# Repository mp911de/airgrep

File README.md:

# airgrep

A portable ADS-B / FLARM receiver. Started as carrier board for a removable ESP32-S3 touch display and ADSBee 1090U receiver, with a soldered MAX-M10S GNSS receiver. It adds a single-cell Li-ion charger, a 5 V boost rail, a fuel gauge, a barometer and a buzzer.

## Current state

- Schematic (7 sheets) and board (105 x 95 mm, 4 layers, all SMD parts on top) are implemented. The active TI PCB and schematics define the hardware; `tools/check.sh` reports the ERC, DRC and parity state.
- Order status and open work are in [docs/open-issues.md](docs/open-issues.md).

## Where things are

| Path | Content |
|---|---|
| [docs/requirements.md](docs/requirements.md) | What the device must do. Read first. |
| [docs/checklist-draft.md](docs/checklist-draft.md) | Draft hardware review checks, investigation guidance and trial evaluation |
| [docs/specs.md](docs/specs.md) | Technical data: radio, charging, battery, power budget, runtimes and validation limits |
| [docs/decisions.md](docs/decisions.md) | Reasons behind the design decisions |
| [docs/mechanical.md](docs/mechanical.md) | Board outline, mounting holes, module placement, battery, antennas, enclosure |
| [docs/interfaces.md](docs/interfaces.md) | Pin maps of the modules and the carrier connectors |
| [docs/i2c-bus-requirements.md](docs/i2c-bus-requirements.md) | I2C speed, bandwidth, capacitance and pull-up limits |
| [docs/firmware.md](docs/firmware.md) | What the display firmware must do: operating modes, charger host control, charger-mode display, sleep |
| [docs/bom-hand-sourced.md](docs/bom-hand-sourced.md) | Parts to buy and fit by hand, with order links and order status |
| [docs/open-issues.md](docs/open-issues.md) | Open work only |
| [issues/](issues/) | Local issue tracker, one markdown file per issue |
| `specs/power_params.json`, `tools/power_budget.py` | Power model inputs and the script that generates the power, runtime and charging tables in `docs/specs.md` |
| `hardware/carrier-ti-charger/` | Active KiCad 10 project `carrier.kicad_pro`, BQ25798 charger. `lib/` holds symbols, footprints and 3D models, `carrier-schematic.pdf` is the schematic print, `jlcpcb/` holds the production exports. |
| `hardware/carrier-max-charger/` | Frozen MAX77757 reference, no further development. Legacy tools and results remain available with `--project NAME`. |
| `hardware/insulator/` | KiCad project of the insulator board between carrier and battery, generated by `tools/make_insulator.py` |
| `hardware/sim/` | Verification by simulation, see [hardware/sim/README.md](hardware/sim/README.md): charge cut-off (`run_thermal.py`), converters and undervoltage latch (`run_power.py`), board heat (`run_heat.py`), emissions and receiver desense (`run_emi.py`), enclosure vents (`vent_model.py`). Active results use the `ti` suffix or `heat/ti/`; MAX results are historical. |
| `mechanical/` | Placement drawing (`placement.png`, `placement.svg`, generator `draw_placement.py`) and extracted module geometry (JSON) |
| `datasheets/` | Data sheets of the parts in use, see [datasheets/README.md](datasheets/README.md) |
| `sources/` | Manufacturer CAD: display KiCad project (`display.zip`), GNSS and gauge Eagle files, ADSBee reference image and schematic text |
| `tools/` | Scripts: design check (`check.sh`), board queries (`board.py`), net-coloured copper maps (`netmap.py`), power budget, CPL correction for JLCPCB (`fix_cpl.py`), insulator generator |

## Tools

- KiCad 10.0.6, including `kicad-cli` and its bundled Python for the scripts that use `pcbnew`. `tools/kpy` runs that Python.
- Python 3.14; the simulation packages are listed in `hardware/sim/requirements.txt`
- ngspice 47 (Homebrew) for `hardware/sim/`
- `python3 tools/report-holes-vias.py path/to/board.kicad_pcb` reports via copper/drill sizes, minimum nominal annular rings, plated and non-plated footprint drills, slots, counts and nets in mil. Edge.Cuts cutouts are excluded.
- `python3 tools/report-traces.py path/to/board.kicad_pcb` reports straight and arc track widths by layer, with counts and nets in mil. Both reports are read-only, sorted by size, and automatically use `tools/kpy` when needed.

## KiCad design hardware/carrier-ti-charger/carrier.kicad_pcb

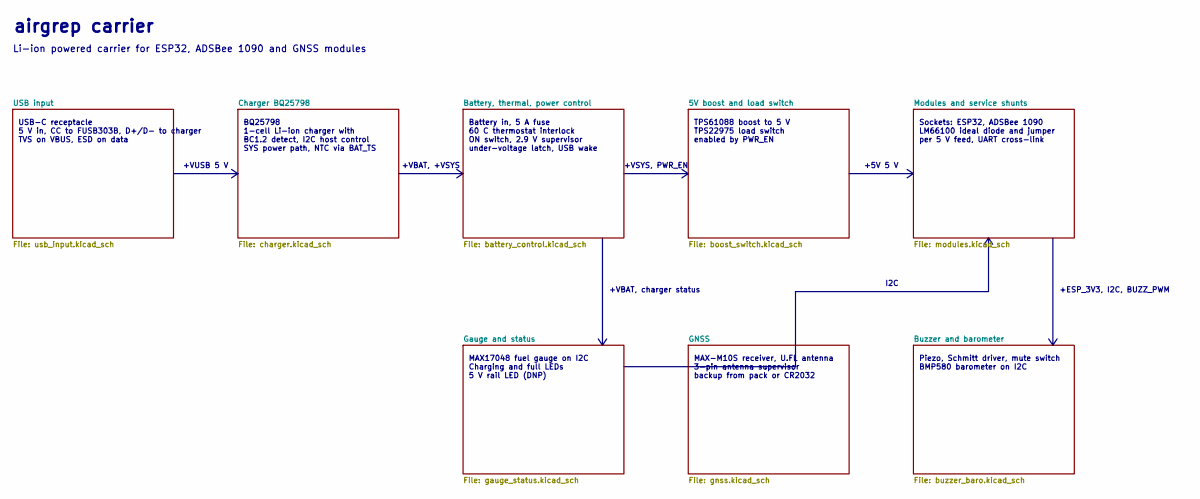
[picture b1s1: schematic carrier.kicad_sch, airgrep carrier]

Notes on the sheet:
I2C
TPS61088 boost to 5 V TPS22975 load switch enabled by PWR_EN
Piezo, Schmitt driver, mute switch BMP580 barometer on I2C
BQ25798 1-cell Li-ion charger with BC1.2 detect, I2C host control SYS power path, NTC via BAT_TS
airgrep carrier
+VBAT, +VSYS
+ESP_3V3, I2C, BUZZ_PWM
+VBAT, charger status
Sockets: ESP32, ADSBee 1090 LM66100 ideal diode and jumper per 5 V feed, UART cross-link
Battery in, 5 A fuse 60 C thermostat interlock ON switch, 2.9 V supervisor under-voltage latch, USB wake
MAX-M10S receiver, U.FL antenna 3-pin antenna supervisor backup from pack or CR2032
+VUSB 5 V
+5V 5 V
USB-C receptacle 5 V in, CC to FUSB303B, D+/D- to charger TVS on VBUS, ESD on data
MAX17048 fuel gauge on I2C Charging and full LEDs 5 V rail LED (DNP)
+VSYS, PWR_EN
Li-ion powered carrier for ESP32, ADSBee 1090 and GNSS modules

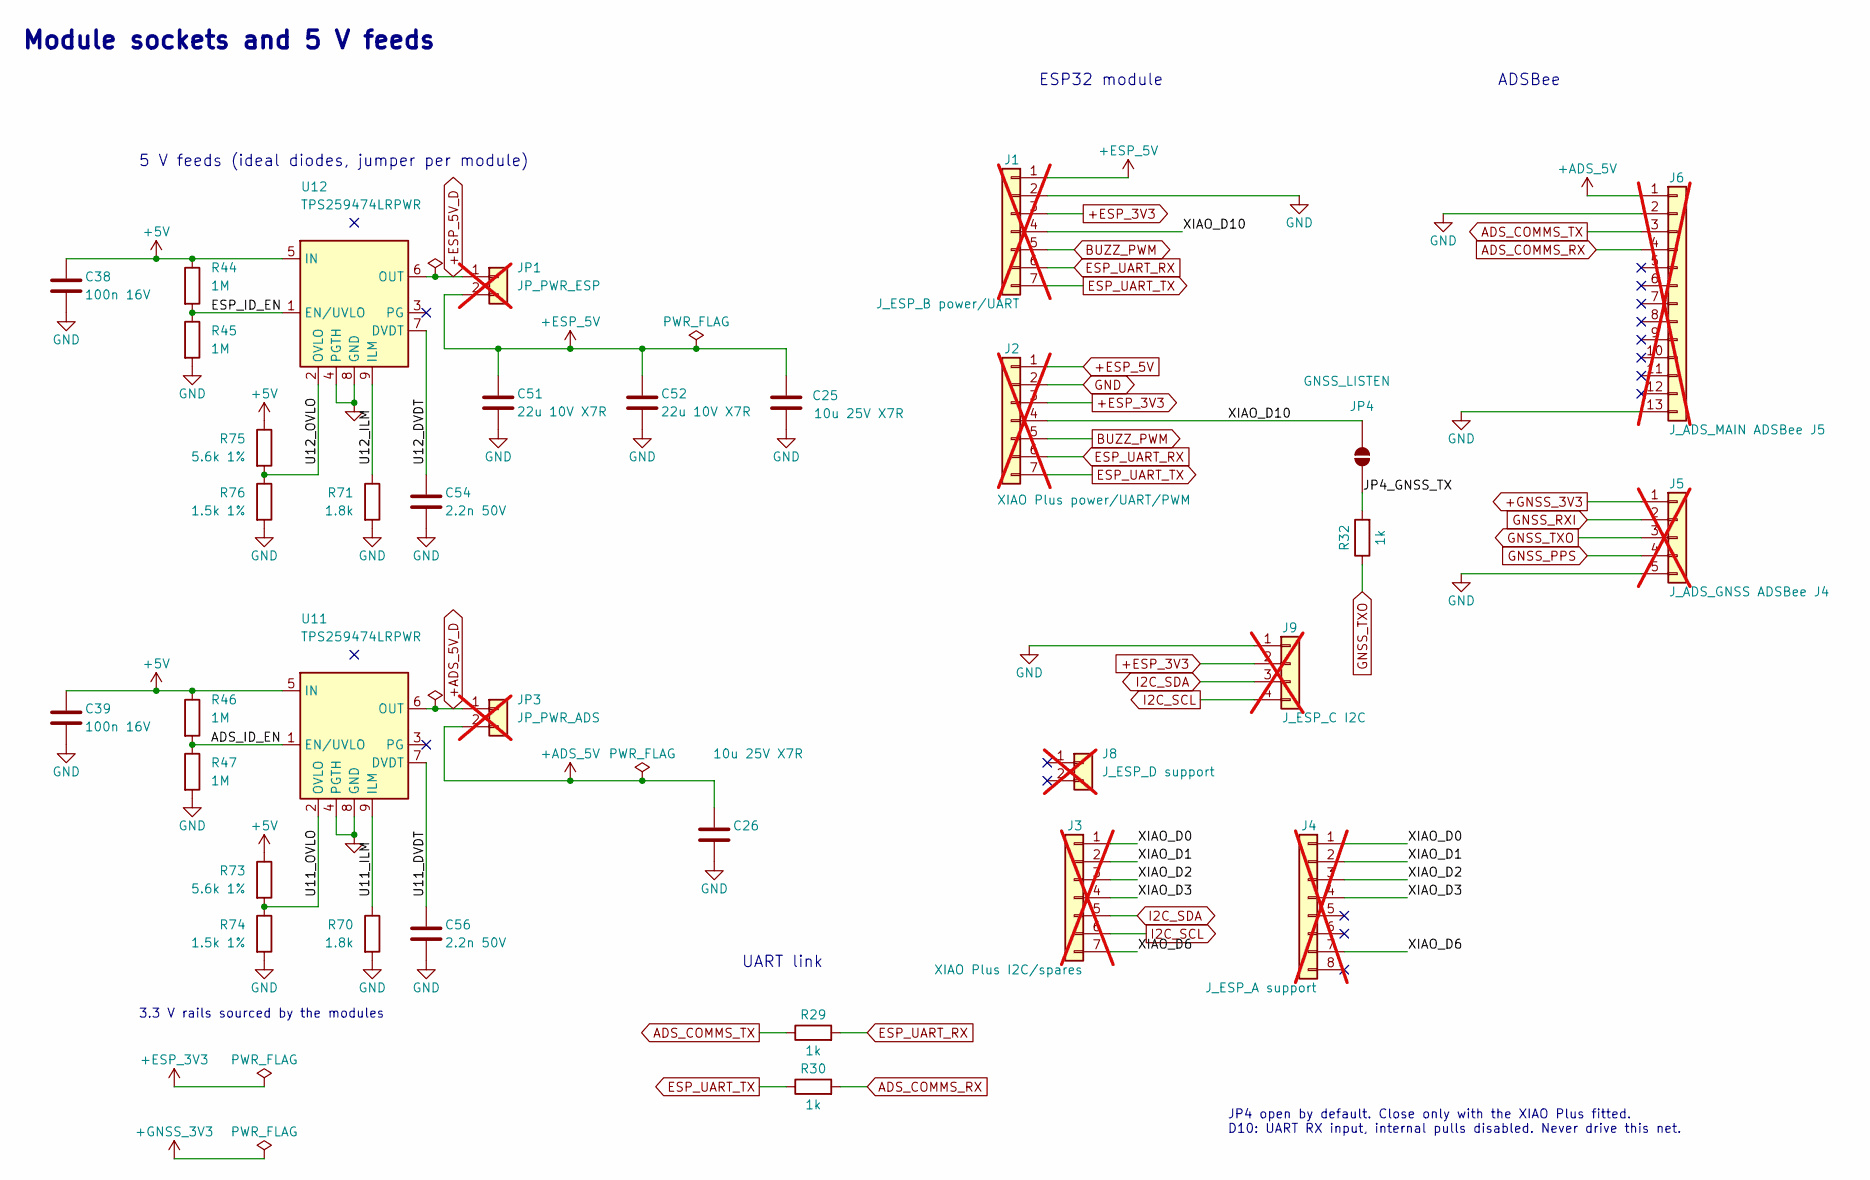
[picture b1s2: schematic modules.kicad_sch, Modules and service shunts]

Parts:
C25, C26: 10u 25V X7R; C_0805_2012Metric; LCSC C3039694
C38, C39: 100n 16V; C_0402_1005Metric_NoSilk; MPN CL05B104KO5NNNC; LCSC C1525
C51, C52: 22u 10V X7R; C_0805_2012Metric; LCSC C907991
C54, C56: 2.2n 50V; C_0603_1608Metric; MPN 0603B222K500NT; LCSC C1604
J1: J_ESP_B power/UART; PinSocket_1x07_P2.54mm_Vertical; not fitted
J2: XIAO Plus power/UART/PWM; PinHeader_1x07_P2.54mm_Vertical; not fitted
J3: XIAO Plus I2C/spares; PinHeader_1x07_P2.54mm_Vertical; not fitted
J4: J_ESP_A support; PinSocket_1x08_P2.54mm_Vertical; not fitted
J5: J_ADS_GNSS ADSBee J4; PinSocket_1x05_P2.54mm_Vertical; not fitted
J6: J_ADS_MAIN ADSBee J5; PinSocket_1x13_P2.54mm_Vertical; not fitted
J8: J_ESP_D support; PinSocket_1x02_P2.54mm_Vertical; not fitted
J9: J_ESP_C I2C; PinSocket_1x04_P2.54mm_Vertical; not fitted
JP1: JP_PWR_ESP; PinHeader_1x02_P2.54mm_Vertical; not fitted
JP3: JP_PWR_ADS; PinHeader_1x02_P2.54mm_Vertical; not fitted
JP4: GNSS_LISTEN; SolderJumper-2_P1.3mm_Open_RoundedPad1.0x1.5mm
R29, R30, R32: 1k; R_0603_1608Metric; LCSC C21190
R44, R45, R46, R47: 1M; R_0603_1608Metric; LCSC C22935
R70, R71: 1.8k; R_0603_1608Metric; Tolerance 1%; MPN 0603WAF1801T5E; LCSC C4177
R73, R75: 5.6k 1%; R_0603_1608Metric; Tolerance 1%; MPN 0603WAF5601T5E; LCSC C23189
R74, R76: 1.5k 1%; R_0402_1005Metric_NoSilk; Tolerance 1%; MPN 0402WGF1501TCE; LCSC C25867
U11, U12: TPS259474LRPWR; VQFN-10_L2.0-W2.0-P0.45-HR_LM73100; LCSC C2864845

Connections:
+5V: C38.1, C39.1, R44.1, R46.1, R73.1, R75.1, U11.5 (IN), U12.5 (IN); also elsewhere on the board
+ADS_5V: C26.1, J6.1, JP3.2
+ADS_5V_D: JP3.1, U11.6 (OUT)
+ESP_3V3: J1.3, J2.3, J9.2; also elsewhere on the board
+ESP_5V: C25.1, C51.1, C52.1, J1.1, J2.1, JP1.2
+ESP_5V_D: JP1.1, U12.6 (OUT); also elsewhere on the board
+GNSS_3V3: J5.1; also elsewhere on the board
/Modules and service shunts/ADS_ID_EN: R46.2, R47.1, U11.1 (EN/UVLO)
/Modules and service shunts/ESP_ID_EN: R44.2, R45.1, U12.1 (EN/UVLO)
/Modules and service shunts/JP4_GNSS_TX: JP4.1 (A), R32.2
/Modules and service shunts/U11_DVDT: C56.1, U11.7 (DVDT)
/Modules and service shunts/U11_ILM: R70.1, U11.9 (ILM)
/Modules and service shunts/U11_OVLO: R73.2, R74.1, U11.2 (OVLO)
/Modules and service shunts/U12_DVDT: C54.1, U12.7 (DVDT)
/Modules and service shunts/U12_ILM: R71.1, U12.9 (ILM)
/Modules and service shunts/U12_OVLO: R75.2, R76.1, U12.2 (OVLO)
/Modules and service shunts/XIAO_D0: J3.1, J4.1
/Modules and service shunts/XIAO_D1: J3.2, J4.2
/Modules and service shunts/XIAO_D2: J3.3, J4.3
/Modules and service shunts/XIAO_D3: J3.4, J4.4
/Modules and service shunts/XIAO_D6: J3.7, J4.7
/Modules and service shunts/XIAO_D10: J1.4, J2.4, JP4.2 (B)
ADS_COMMS_RX: J6.4, R30.2
ADS_COMMS_TX: J6.3, R29.1
BUZZ_PWM: J1.5, J2.5; also elsewhere on the board
ESP_UART_RX: J1.6, J2.6, R29.2
ESP_UART_TX: J1.7, J2.7, R30.1
GND: C25.2, C26.2, C38.2, C39.2, C51.2, C52.2, C54.2, C56.2, J1.2, J2.2, J5.5, J6.2, J6.13, J9.1, R45.2, R47.2, R70.2, R71.2, R74.2, R76.2, U11.4 (PGTH), U11.8 (GND), U12.4 (PGTH), U12.8 (GND); also elsewhere on the board
GNSS_PPS: J5.4; also elsewhere on the board
GNSS_RXI: J5.2; also elsewhere on the board
GNSS_TXO: J5.3, R32.1; also elsewhere on the board
I2C_SCL: J3.6, J9.4; also elsewhere on the board
I2C_SDA: J3.5, J9.3; also elsewhere on the board

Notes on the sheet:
Module sockets and 5 V feeds
UART link
ADSBee
3.3 V rails sourced by the modules
JP4 open by default. Close only with the XIAO Plus fitted. D10: UART RX input, internal pulls disabled. Never drive this net.
5 V feeds (ideal diodes, jumper per module)
ESP32 module

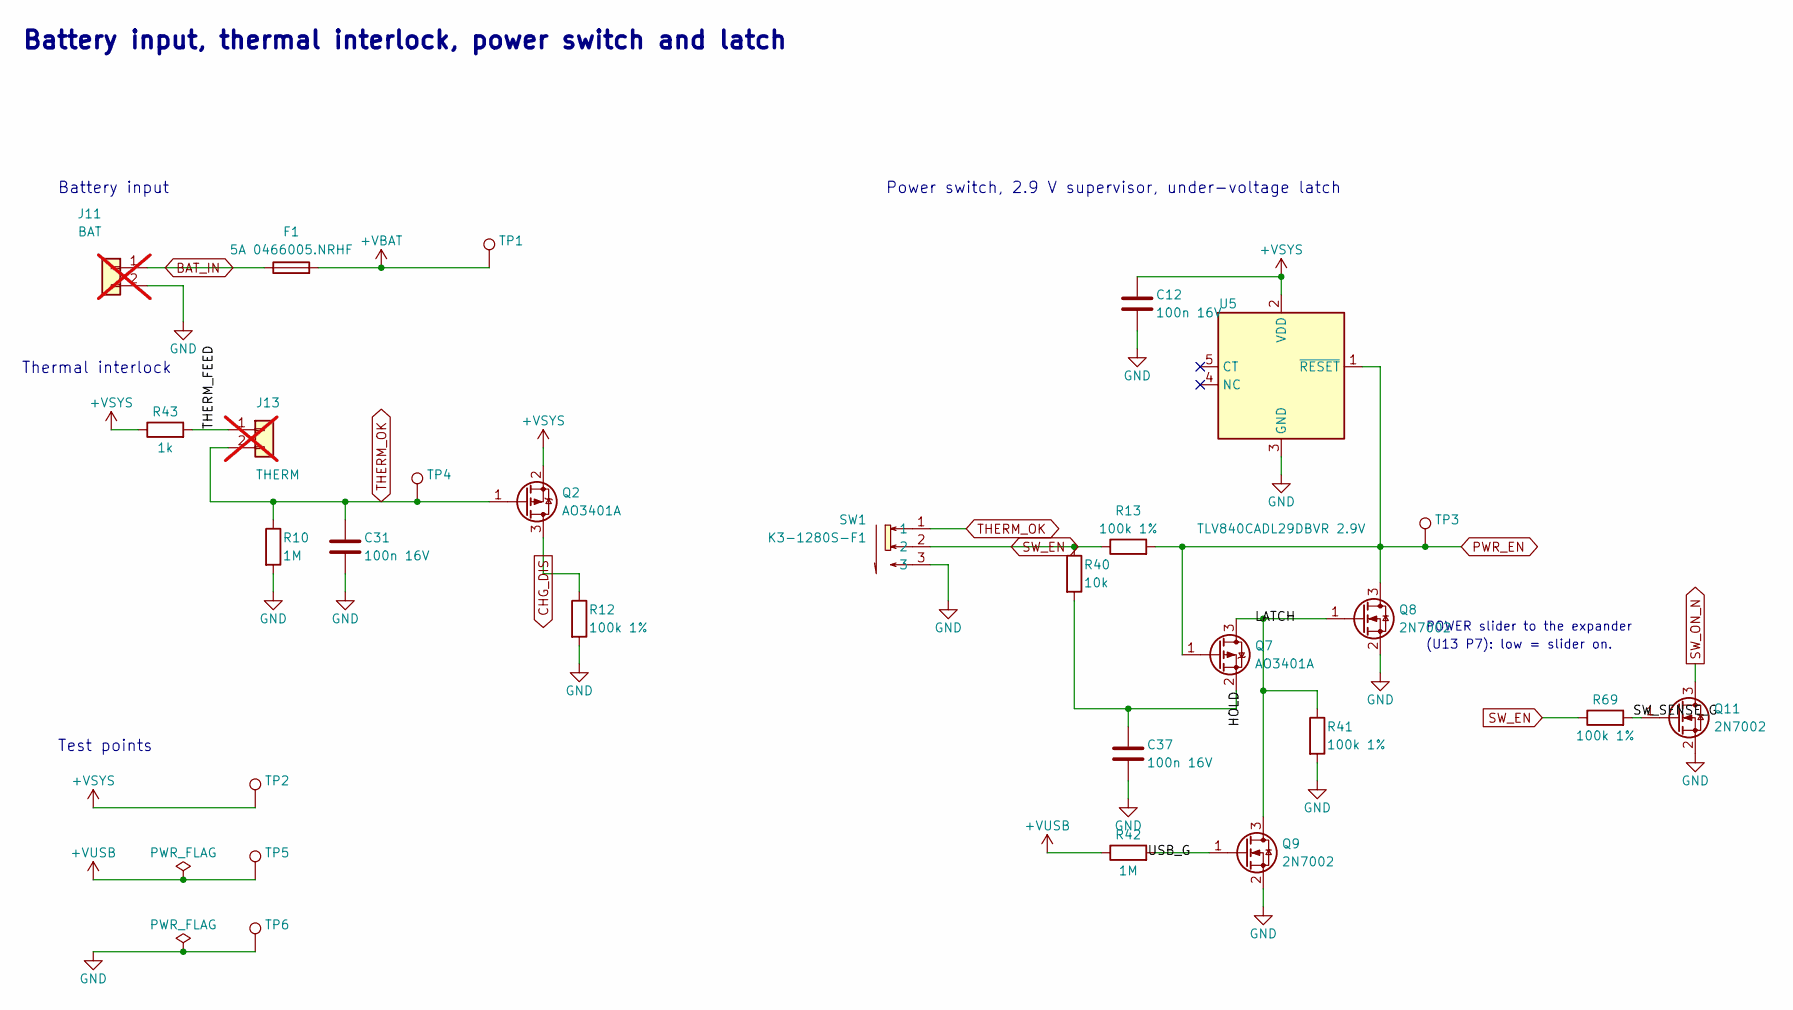
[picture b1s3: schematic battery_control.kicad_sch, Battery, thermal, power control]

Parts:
C12, C31, C37: 100n 16V; C_0402_1005Metric_NoSilk; MPN CL05B104KO5NNNC; LCSC C1525
F1: 5A 0466005.NRHF; Fuse_1206_3216Metric; LCSC C57525
J11: BAT; JST_PH_B2B-PH-K_1x02_P2.00mm_Vertical_R10; not fitted
J13: THERM; JST_PH_B2B-PH-K_1x02_P2.00mm_Vertical_R10; not fitted
Q2, Q7: AO3401A; SOT-23; LCSC C15127
Q8, Q9, Q11: 2N7002; SOT-23; LCSC C8545
R10, R42: 1M; R_0603_1608Metric; LCSC C22935
R12, R13, R41, R69: 100k 1%; R_0603_1608Metric; LCSC C25803
R40: 10k; R_0603_1608Metric; LCSC C25804
R43: 1k; R_0603_1608Metric; LCSC C21190
SW1: K3-1280S-F1; SW-SMD_K3-1280S-F1; LCSC C92658
TP1: +VBAT; TestPoint_Pad_D1.5mm
TP2: +VSYS; TestPoint_Pad_D1.5mm
TP3: PWR_EN; TestPoint_Pad_D1.5mm
TP4: THERM_OK; TestPoint_Pad_D1.5mm
TP5: +VUSB; TestPoint_Pad_D1.5mm
TP6: GND; TestPoint_Pad_D1.5mm
U5: TLV840CADL29DBVR 2.9V; SOT-23-5_L2.9-W1.6-P0.95-LS2.8-BR; LCSC C3686404

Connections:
+VBAT: F1.2, TP1.1 (1_1); also elsewhere on the board
+VSYS: C12.1, Q2.2 (S), R43.1, TP2.1 (1_1), U5.2 (VDD); also elsewhere on the board
+VUSB: R42.1, TP5.1 (1_1); also elsewhere on the board
/Battery, thermal, power control/HOLD: C37.2, Q7.2 (S), R40.2
/Battery, thermal, power control/LATCH: Q7.3 (D), Q8.1 (G), Q9.3 (D), R41.1
/Battery, thermal, power control/SW_SENSE_G: Q11.1 (G), R69.2
/Battery, thermal, power control/THERM_FEED: J13.1, R43.2
/Battery, thermal, power control/USB_G: Q9.1 (G), R42.2
BAT_IN: F1.1, J11.1
CHG_DIS: Q2.3 (D), R12.1; also elsewhere on the board
GND: C12.2, C31.2, C37.1, J11.2, Q8.2 (S), Q9.2 (S), Q11.2 (S), R10.2, R12.2, R41.2, SW1.3, TP6.1 (1_1), U5.3 (GND); also elsewhere on the board
PWR_EN: Q7.1 (G), Q8.3 (D), R13.2, TP3.1 (1_1), U5.1 (~RESET); also elsewhere on the board
SW_EN: R13.1, R40.1, R69.1, SW1.2; also elsewhere on the board
SW_ON_N: Q11.3 (D); also elsewhere on the board
THERM_OK: C31.1, J13.2, Q2.1 (G), R10.1, SW1.1, TP4.1 (1_1)

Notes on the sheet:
Battery input
Battery input, thermal interlock, power switch and latch
Power switch, 2.9 V supervisor, under-voltage latch
Test points
(U13 P7): low = slider on.
Thermal interlock
POWER slider to the expander

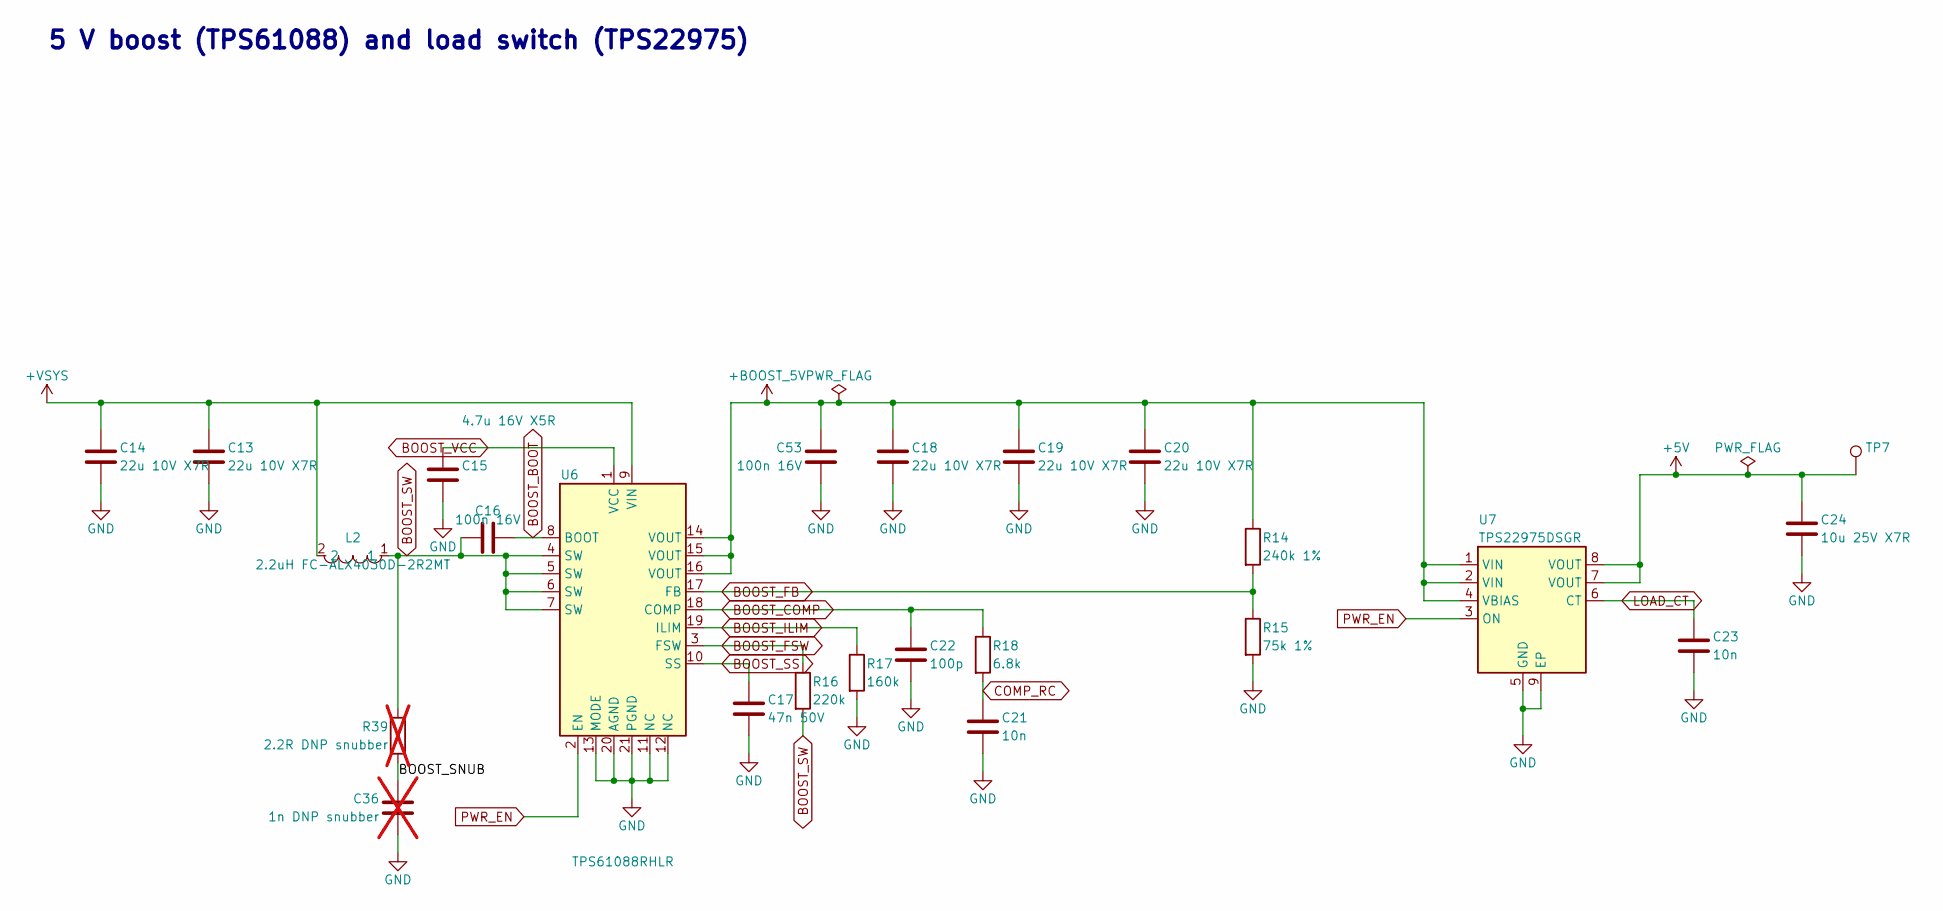
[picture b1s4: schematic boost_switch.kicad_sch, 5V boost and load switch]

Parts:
C13, C14, C18, C19, C20: 22u 10V X7R; C_0805_2012Metric; LCSC C907991
C15: 4.7u 16V X5R; C_0603_1608Metric; LCSC C19666
C16, C53: 100n 16V; C_0402_1005Metric_NoSilk; MPN CL05B104KO5NNNC; LCSC C1525
C17: 47n 50V; C_0603_1608Metric; LCSC C1622
C21, C23: 10n; C_0603_1608Metric; LCSC C57112
C22: 100p; C_0603_1608Metric; LCSC C14858
C24: 10u 25V X7R; C_0805_2012Metric; LCSC C3039694
C36: 1n DNP snubber; C_0603_1608Metric; not fitted
L2: 2.2uH FC-ALX4030D-2R2MT; IND-SMD_L4.2-W4.2_FC-ALX4030D; LCSC C5370906
R14: 240k 1%; R_0603_1608Metric; LCSC C4197
R15: 75k 1%; R_0603_1608Metric; LCSC C23242
R16: 220k; R_0603_1608Metric; LCSC C22961
R17: 160k; R_0603_1608Metric; LCSC C22813
R18: 6.8k; R_0603_1608Metric; LCSC C23212
R39: 2.2R DNP snubber; R_0603_1608Metric; not fitted
TP7: +5V; TestPoint_Pad_D1.5mm
U6: TPS61088RHLR; VQFN-20_L4.6-W3.6-P0.50-BL; LCSC C87357
U7: TPS22975DSGR; Texas_DSG0008A_WSON-8-1EP_2x2mm_P0.5mm_EP0.9x1.6mm; LCSC C524777

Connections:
+5V: C24.1, TP7.1 (1_1), U7.7 (VOUT), U7.8 (VOUT); also elsewhere on the board
+BOOST_5V: C18.1, C19.1, C20.1, C53.1, R14.1, U6.14 (VOUT), U6.15 (VOUT), U6.16 (VOUT), U7.1 (VIN), U7.2 (VIN), U7.4 (VBIAS)
+VSYS: C13.1, C14.1, L2.2, U6.9 (VIN); also elsewhere on the board
/5V boost and load switch/BOOST_SNUB: C36.1, R39.2
BOOST_BOOT: C16.1, U6.8 (BOOT)
BOOST_COMP: C22.1, R18.1, U6.18 (COMP)
BOOST_FB: R14.2, R15.1, U6.17 (FB)
BOOST_FSW: R16.1, U6.3 (FSW)
BOOST_ILIM: R17.1, U6.19 (ILIM)
BOOST_SS: C17.1, U6.10 (SS)
BOOST_SW: C16.2, L2.1, R16.2, R39.1, U6.4 (SW), U6.5 (SW), U6.6 (SW), U6.7 (SW)
BOOST_VCC: C15.1, U6.1 (VCC)
COMP_RC: C21.1, R18.2
GND: C13.2, C14.2, C15.2, C17.2, C18.2, C19.2, C20.2, C21.2, C22.2, C23.2, C24.2, C36.2, C53.2, R15.2, R17.2, U6.11 (NC), U6.12 (NC), U6.13 (MODE), U6.20 (AGND), U6.21 (PGND), U7.5 (GND), U7.9 (EP); also elsewhere on the board
LOAD_CT: C23.1, U7.6 (CT)
PWR_EN: U6.2 (EN), U7.3 (ON); also elsewhere on the board

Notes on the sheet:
5 V boost (TPS61088) and load switch (TPS22975)

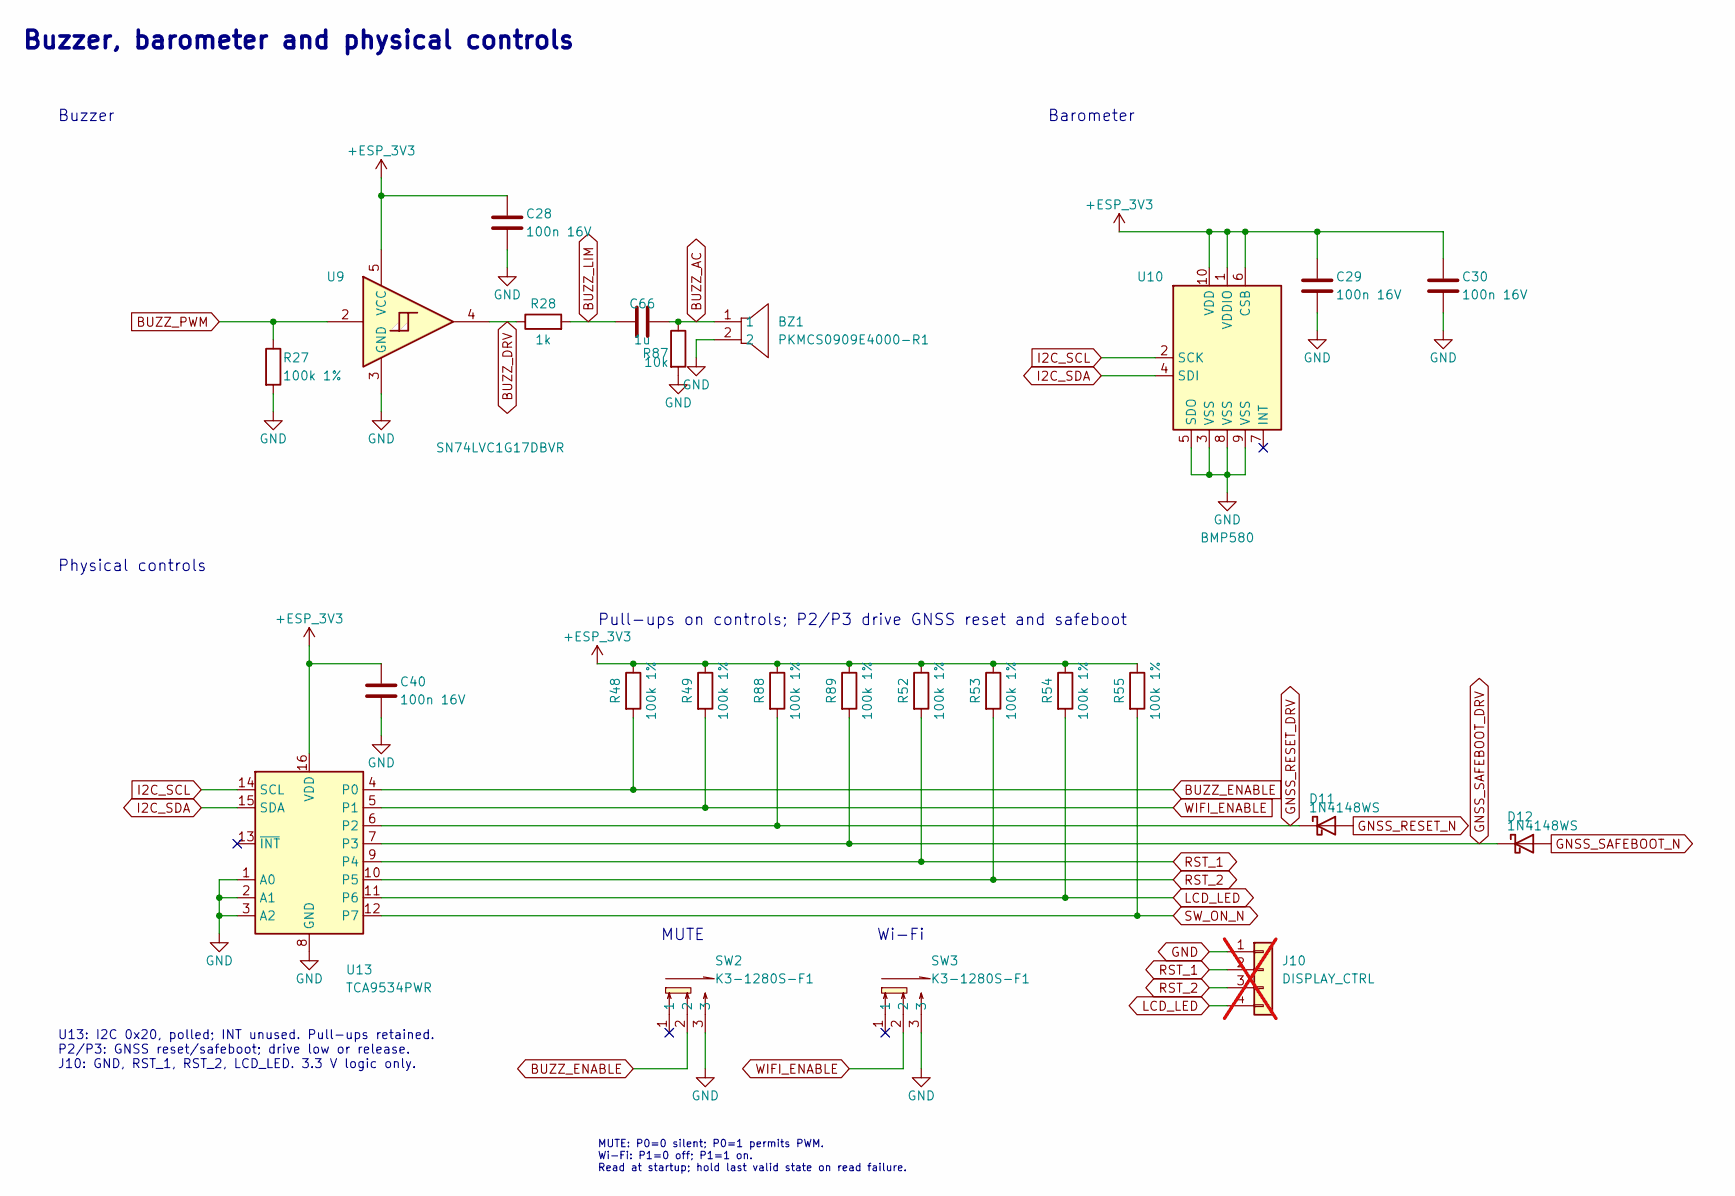
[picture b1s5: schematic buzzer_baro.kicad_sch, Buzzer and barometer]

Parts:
BZ1: PKMCS0909E4000-R1; BUZ-SMD_L9.0-W9.0_PKMCS0909E4000-R1; LCSC C910763
C28, C29, C30, C40: 100n 16V; C_0402_1005Metric_NoSilk; MPN CL05B104KO5NNNC; LCSC C1525
C66: 1u; C_0603_1608Metric; MPN CL10A105KB8NNNC; LCSC C15849
D11, D12: 1N4148WS; D_SOD-323; MPN 1N4148WS; LCSC C2128
J10: DISPLAY_CTRL; PinHeader_1x04_P2.54mm_Vertical; not fitted
R27, R48, R49, R52, R53, R54, R55, R88, R89: 100k 1%; R_0603_1608Metric; LCSC C25803
R28: 1k; R_0603_1608Metric; LCSC C21190
R87: 10k; R_0402_1005Metric_NoSilk; MPN 0402WGF1002TCE; LCSC C25744
SW2, SW3: K3-1280S-F1; SW-SMD_K3-1280S-F1; LCSC C92658
U9: SN74LVC1G17DBVR; SOT-23-5; LCSC C7836
U10: BMP580; LGA-10_L2.0-W2.0-P0.50-TL_BMP581; MPN BMP580; LCSC C22391138
U13: TCA9534PWR; TSSOP-16_4.4x5mm_P0.65mm; LCSC C783615

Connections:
+ESP_3V3: C28.1, C29.1, C30.1, C40.1, R48.1, R49.1, R52.1, R53.1, R54.1, R55.1, R88.1, R89.1, U9.5 (VCC), U10.1 (VDDIO), U10.6 (CSB), U10.10 (VDD), U13.16 (VDD); also elsewhere on the board
BUZZ_AC: BZ1.1, C66.2, R87.1
BUZZ_DRV: R28.1, U9.4
BUZZ_ENABLE: R48.2, SW2.2, U13.4 (P0)
BUZZ_LIM: C66.1, R28.2
BUZZ_PWM: R27.1, U9.2; also elsewhere on the board
GND: BZ1.2, C28.2, C29.2, C30.2, C40.2, J10.1, R27.2, R87.2, SW2.3, SW3.3, U9.3 (GND), U10.3 (VSS), U10.5 (SDO), U10.8 (VSS), U10.9 (VSS), U13.1 (A0), U13.2 (A1), U13.3 (A2), U13.8 (GND); also elsewhere on the board
GNSS_RESET_DRV: D11.1 (K), R88.2, U13.6 (P2)
GNSS_RESET_N: D11.2 (A); also elsewhere on the board
GNSS_SAFEBOOT_DRV: D12.1 (K), R89.2, U13.7 (P3)
GNSS_SAFEBOOT_N: D12.2 (A); also elsewhere on the board
I2C_SCL: U10.2 (SCK), U13.14 (SCL); also elsewhere on the board
I2C_SDA: U10.4 (SDI), U13.15 (SDA); also elsewhere on the board
LCD_LED: J10.4, R54.2, U13.11 (P6)
RST_1: J10.2, R52.2, U13.9 (P4)
RST_2: J10.3, R53.2, U13.10 (P5)
SW_ON_N: R55.2, U13.12 (P7); also elsewhere on the board
WIFI_ENABLE: R49.2, SW3.2, U13.5 (P1)

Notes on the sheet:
Wi-Fi
Barometer
MUTE: P0=0 silent; P0=1 permits PWM. Wi-Fi: P1=0 off; P1=1 on. Read at startup; hold last valid state on read failure.
Buzzer, barometer and physical controls
Physical controls
U13: I2C 0x20, polled; INT unused. Pull-ups retained. P2/P3: GNSS reset/safeboot; drive low or release. J10: GND, RST_1, RST_2, LCD_LED. 3.3 V logic only.
Pull-ups on controls; P2/P3 drive GNSS reset and safeboot
Buzzer
MUTE

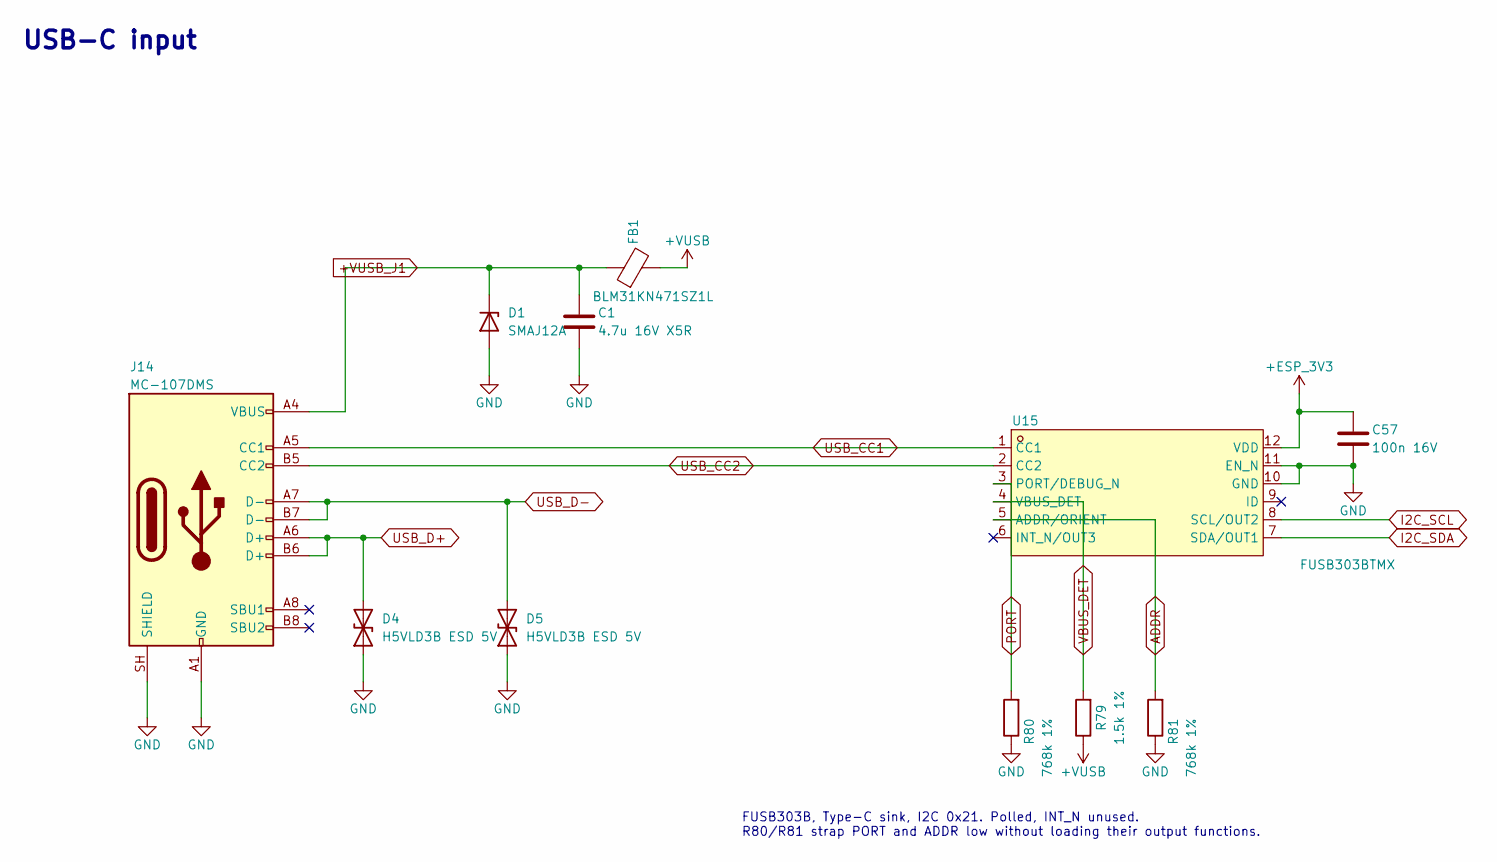
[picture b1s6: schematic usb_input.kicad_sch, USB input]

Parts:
C1: 4.7u 16V X5R; C_0603_1608Metric; LCSC C19666
C57: 100n 16V; C_0402_1005Metric_NoSilk; MPN CL05B104KO5NNNC; LCSC C1525
D1: SMAJ12A; D_SMA; LCSC C19077531
D4, D5: H5VLD3B ESD 5V; D_SOD-323; MPN H5VLD3B; LCSC C20615805
FB1: BLM31KN471SZ1L; L_1206_3216Metric; LCSC C710518
J14: MC-107DMS; USB_C_Receptacle_Hanbo_MC-107DMS; LCSC C3039295
R79: 1.5k 1%; R_0402_1005Metric_NoSilk; MPN 0402WGF1501TCE; LCSC C25867
R80, R81: 768k 1%; R_0402_1005Metric_NoSilk; MPN FRC0402F7683TS; LCSC C49196905
U15: FUSB303BTMX; X2QFN-12_L1.6-W1.6-P0.40-TL; LCSC C895444

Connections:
+ESP_3V3: C57.1, U15.12 (VDD); also elsewhere on the board
+VUSB: FB1.2, R79.1; also elsewhere on the board
+VUSB_J1: C1.1, D1.1 (K), FB1.1, J14.A4 (VBUS), J14.A9 (VBUS), J14.B4 (VBUS), J14.B9 (VBUS)
ADDR: R81.2, U15.5 (ADDR/ORIENT)
GND: C1.2, C57.2, D1.2 (A), D4.1 (A1), D5.1 (A1), J14.A1 (GND), J14.A12 (GND), J14.B1 (GND), J14.B12 (GND), J14.SH (SHIELD), R80.1, R81.1, U15.10 (GND), U15.11 (EN_N); also elsewhere on the board
I2C_SCL: U15.8 (SCL/OUT2); also elsewhere on the board
I2C_SDA: U15.7 (SDA/OUT1); also elsewhere on the board
PORT: R80.2, U15.3 (PORT/DEBUG_N)
USB_CC1: J14.A5 (CC1), U15.1 (CC1)
USB_CC2: J14.B5 (CC2), U15.2 (CC2)
USB_D+: D4.2 (A2), J14.A6 (D+), J14.B6 (D+); also elsewhere on the board
USB_D-: D5.2 (A2), J14.A7 (D-), J14.B7 (D-); also elsewhere on the board
VBUS_DET: R79.2, U15.4 (VBUS_DET)

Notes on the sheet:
USB-C input
FUSB303B, Type-C sink, I2C 0x21. Polled, INT_N unused. R80/R81 strap PORT and ADDR low without loading their output functions.

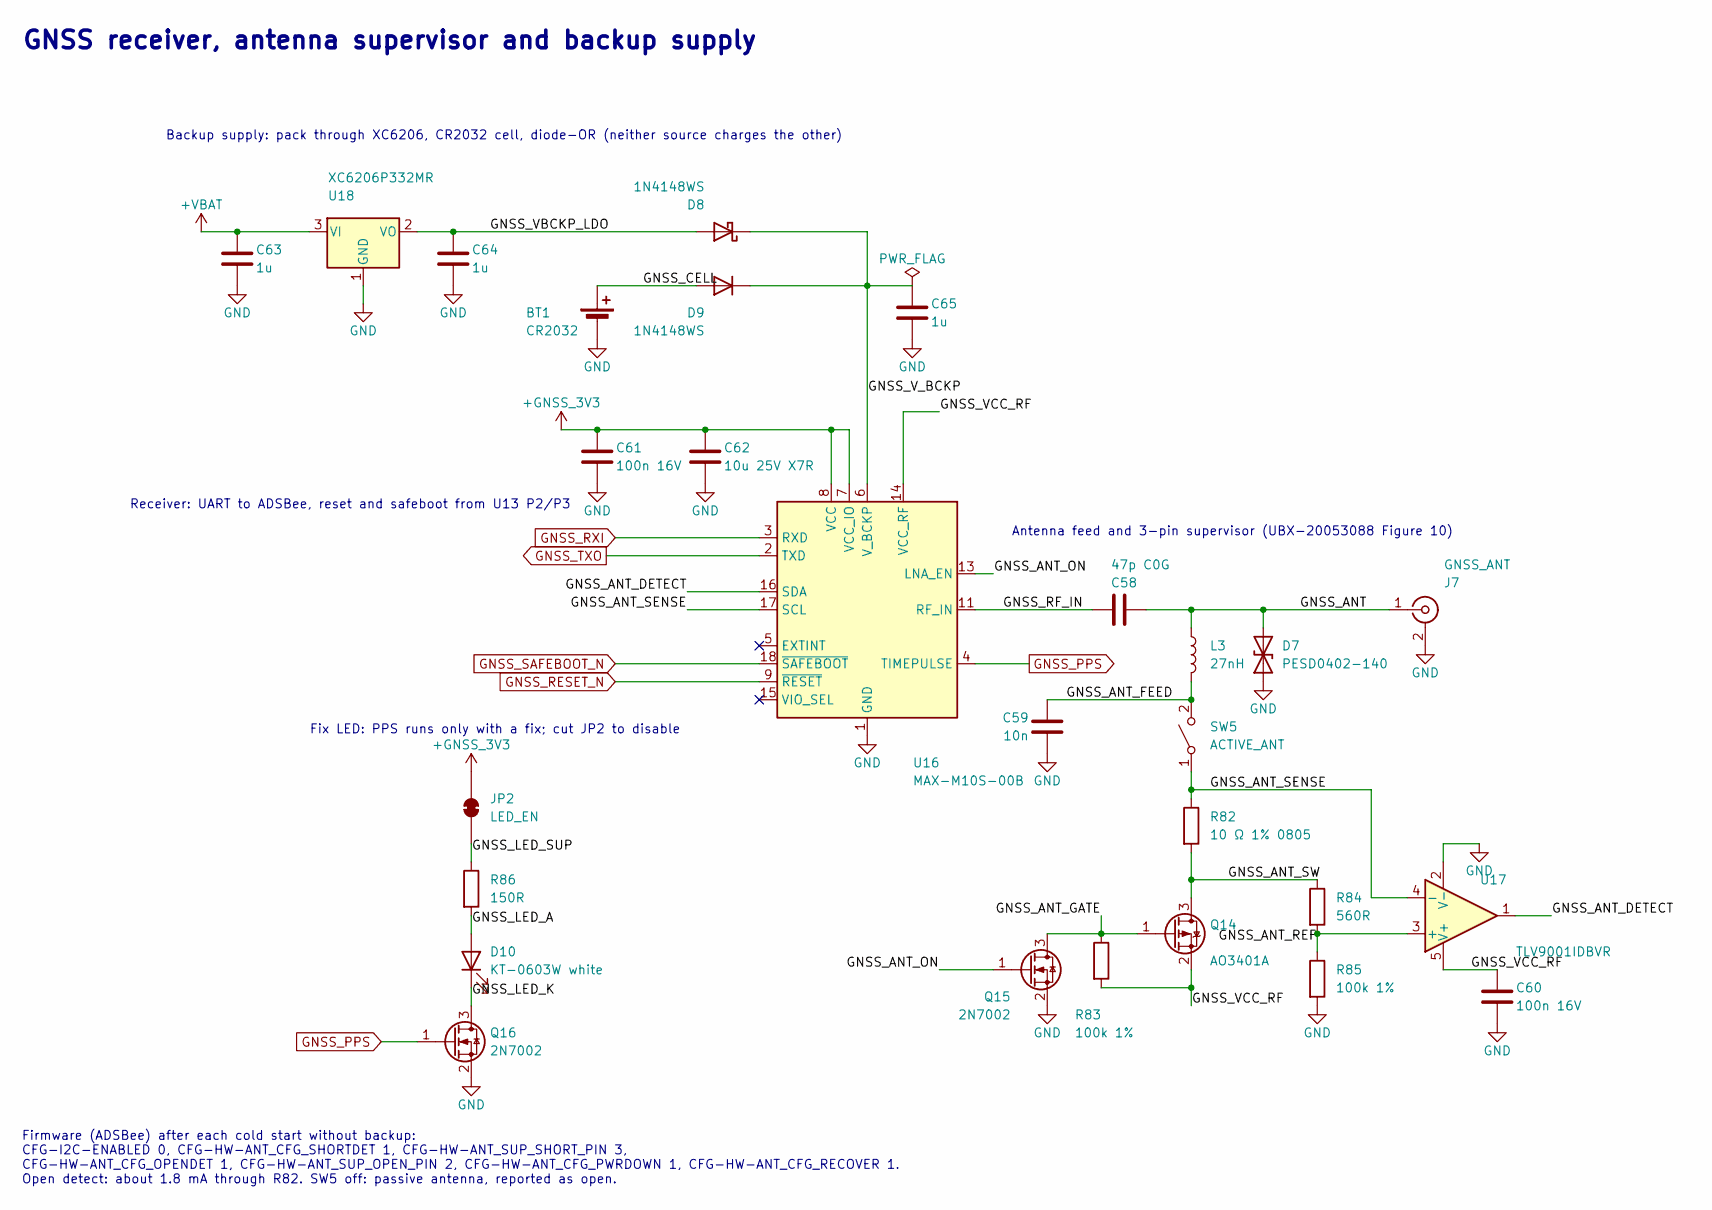
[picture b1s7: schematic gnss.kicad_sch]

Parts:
BT1: CR2032; BAT-SMD_BS-CR2032-8; MPN BS-CR2032-8; LCSC C7498149
C58: 47p C0G; C_0402_1005Metric_NoSilk; MPN 0402CG470J500NT; LCSC C1567
C59: 10n; C_0603_1608Metric; LCSC C57112
C60, C61: 100n 16V; C_0402_1005Metric_NoSilk; MPN CL05B104KO5NNNC; LCSC C1525
C62: 10u 25V X7R; C_0805_2012Metric; MPN CL21B106KAYQNNE; LCSC C3039694
C63, C64, C65: 1u; C_0603_1608Metric; MPN CL10A105KB8NNNC; LCSC C15849
D7: PESD0402-140; D_0402_1005Metric; MPN PESD0402-140; LCSC C10662
D8, D9: 1N4148WS; D_SOD-323; MPN 1N4148WS; LCSC C2128
D10: KT-0603W white; LED_0603_1608Metric; MPN KT-0603W; LCSC C2290
J7: GNSS_ANT; U.FL_Hirose_U.FL-R-SMT-1_Vertical; MPN U.FL-R-SMT-1(80); LCSC C88374
JP2: LED_EN; SolderJumper-2_P1.3mm_Bridged_RoundedPad1.0x1.5mm
L3: 27nH; L_0402_1005Metric; MPN LQG15HS27NJ02D; LCSC C12669
Q14: AO3401A; SOT-23; MPN AO3401A; LCSC C15127
Q15, Q16: 2N7002; SOT-23; MPN 2N7002; LCSC C8545
R82: 10 Ω 1% 0805; R_0805_2012Metric_NoSilk; LCSC C17415
R83, R85: 100k 1%; R_0603_1608Metric; LCSC C25803
R84: 560R; R_0603_1608Metric; MPN 0603WAF5600T5E; LCSC C23204
R86: 150R; R_0603_1608Metric; LCSC C22808
SW5: ACTIVE_ANT; SW-SMD_SHOUHAN_2.54-1P_TPGT; MPN 2.54-1P TPGT; LCSC C7421519
U16: MAX-M10S-00B; ublox_MAX-M10S; MPN MAX-M10S-00B; LCSC C4153167
U17: TLV9001IDBVR; SOT-23-5; MPN TLV9001IDBVR; LCSC C398363
U18: XC6206P332MR; SOT-23; MPN XC6206P332MR; LCSC C5446

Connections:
+GNSS_3V3: C61.1, C62.1, JP2.2 (B), U16.7 (VCC_IO), U16.8 (VCC); also elsewhere on the board
+VBAT: C63.1, U18.3 (VI); also elsewhere on the board
/GNSS/GNSS_ANT: C58.2, D7.2 (A2), J7.1 (In), L3.1
/GNSS/GNSS_ANT_DETECT: U16.16 (SDA), U17.1
/GNSS/GNSS_ANT_FEED: C59.1, L3.2, SW5.2 (B)
/GNSS/GNSS_ANT_GATE: Q14.1 (G), Q15.3 (D), R83.1
/GNSS/GNSS_ANT_ON: Q15.1 (G), U16.13 (LNA_EN)
/GNSS/GNSS_ANT_REF: R84.2, R85.1, U17.3 (+)
/GNSS/GNSS_ANT_SENSE: R82.1, SW5.1 (A), U16.17 (SCL), U17.4 (-)
/GNSS/GNSS_ANT_SW: Q14.3 (D), R82.2, R84.1
/GNSS/GNSS_CELL: BT1.1 (+), D9.2 (A)
/GNSS/GNSS_LED_A: D10.2 (A), R86.2
/GNSS/GNSS_LED_K: D10.1 (K), Q16.3 (D)
/GNSS/GNSS_LED_SUP: JP2.1 (A), R86.1
/GNSS/GNSS_RF_IN: C58.1, U16.11 (RF_IN)
/GNSS/GNSS_VBCKP_LDO: C64.1, D8.2 (A), U18.2 (VO)
/GNSS/GNSS_VCC_RF: C60.1, Q14.2 (S), R83.2, U16.14 (VCC_RF), U17.5 (V+)
/GNSS/GNSS_V_BCKP: C65.1, D8.1 (K), D9.1 (K), U16.6 (V_BCKP)
GND: BT1.2 (-), C59.2, C60.2, C61.2, C62.2, C63.2, C64.2, C65.2, D7.1 (A1), J7.2 (Ext), Q15.2 (S), Q16.2 (S), R85.2, U16.1 (GND), U16.10 (GND), U16.12 (GND), U17.2 (V-), U18.1 (GND); also elsewhere on the board
GNSS_PPS: Q16.1 (G), U16.4 (TIMEPULSE); also elsewhere on the board
GNSS_RESET_N: U16.9 (~RESET); also elsewhere on the board
GNSS_RXI: U16.3 (RXD); also elsewhere on the board
GNSS_SAFEBOOT_N: U16.18 (~SAFEBOOT); also elsewhere on the board
GNSS_TXO: U16.2 (TXD); also elsewhere on the board

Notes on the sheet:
Antenna feed and 3-pin supervisor (UBX-20053088 Figure 10)
Backup supply: pack through XC6206, CR2032 cell, diode-OR (neither source charges the other)
GNSS receiver, antenna supervisor and backup supply
Fix LED: PPS runs only with a fix; cut JP2 to disable
Firmware (ADSBee) after each cold start without backup: CFG-I2C-ENABLED 0, CFG-HW-ANT_CFG_SHORTDET 1, CFG-HW-ANT_SUP_SHORT_PIN 3, CFG-HW-ANT_CFG_OPENDET 1, CFG-HW-ANT_SUP_OPEN_PIN 2, CFG-HW-ANT_CFG_PWRDOWN 1, CFG-HW-ANT_CFG_RECOVER 1. Open detect: about 1.8 mA through R82. SW5 off: passive antenna,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
Receiver: UART to ADSBee, reset and safeboot from U13 P2/P3
